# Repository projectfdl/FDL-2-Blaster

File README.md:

# FDL-2-Blaster

This is the Git repository for all things FDL-2 related. You can find all the print/STL files you need here to print your own FDL-2 as well as parts lists, wiring diagrams and firmware.

There are technically three versions of the FDL-2. The original FDL-2 with a stepper pusher motor, the FDL-2+ with the DC pusher motor, and the FDL-2X with the OLED screen and click knob.

If you are building an FDL-2+:

If you are building an FDL-2X:

If you are building an FDL-2 Original Stepper version:

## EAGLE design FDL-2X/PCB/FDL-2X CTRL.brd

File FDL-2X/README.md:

# FDL-2X-Blaster

To update FDL-2X firmware you need the following:

[Sparkfun Microview Programmer](https://www.sparkfun.com/products/12924)<br/>
[XLoader](http://xloader.russemotto.com/)<br/>
Windows computer. (There are ways to do this on a mac but I have not found a quick and easy utility to do so)<br/>
<br/>
#### Flashing your FDL-2X</br>
#### Caution!!! Flash your blaster at your own risk. Doing so is not covered by any sort of warranty. If you are not comfortable or 100% confident, consider sending your Microview to Project FDL to flash.</br>
-Remove the rear blaster cap and Microview. <br/>
-Insert the Microview programmer into the USB port on your Windows computer. <br/>
-Insert the Microview from your blaster into the programmer paying careful attention to orientation.<br/>
-The screen on your microview should point up with the USB connector facing left. There is a picture indication on the board as well.<br/>
-Run XLoader. <br/>
-Choose your desired firmware hex file. <br/>
-Select the Duemilanove/Nano(ATmega328) option under device.<br/>
-Choose the com port of your USB programmer.<br/>
-Set baud rate to 115200.<br/>
-Click upload.<br/>
-You should see the lights under the screen flickering. Flashing can take 30 seconds or longer.<br/>
-When flashing is complete you will see the FDL-2X splash screen then the speed menu as usual.<br/>
-Remove the Microview from the programmer and put it back in your FDL-2X.<br/>
-Replace the rear cap and you're good to go.<br/>

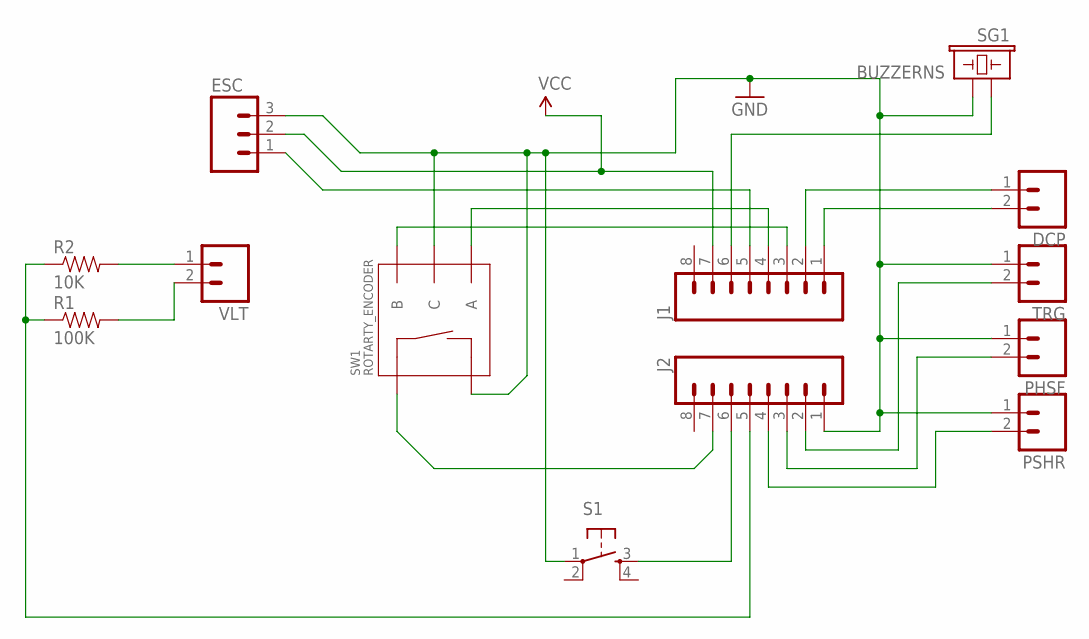
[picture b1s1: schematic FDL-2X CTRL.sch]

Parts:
DCP: M02PTH; 1X02
ESC: M03PTH; 1X03
J1, J2: M08SILK_FEMALE_PTH; 1X08
PHSF: M02PTH; 1X02
PSHR: M02PTH; 1X02
R1: 100K; AXIAL-0.3
R2: 10K; AXIAL-0.3
S1: TAC_SWITCHPTH; TACTILE-PTH
SG1: BUZZERNS; BUZZER-12MM-NS
SW1: ROTARTY_ENCODER; ROTARY_ENC_PLAIN
TRG: M02PTH; 1X02
VLT: M02PTH; 1X02

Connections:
GND: ESC.3, J2.1, PHSF.1, PSHR.1, S1.1, SG1.- (2), SW1.C, SW1.SW-, TRG.1
unnamed: ESC.1, J1.5
unnamed: J2.6, S1.3
unnamed: J2.2, TRG.2
unnamed: J2.3, PHSF.2
unnamed: J2.7, SW1.SW+
unnamed: J2.4, PSHR.2
unnamed: J1.4, SW1.A
unnamed: J1.3, SW1.B
unnamed: DCP.1, J1.2
unnamed: R2.P$2 (2), VLT.1
unnamed: DCP.2, J1.1
unnamed: R1.P$2 (2), VLT.2
unnamed: J1.6, SG1.+ (1)
unnamed: J2.5, R1.P$1 (1), R2.P$1 (1)
VCC: ESC.2, J1.7

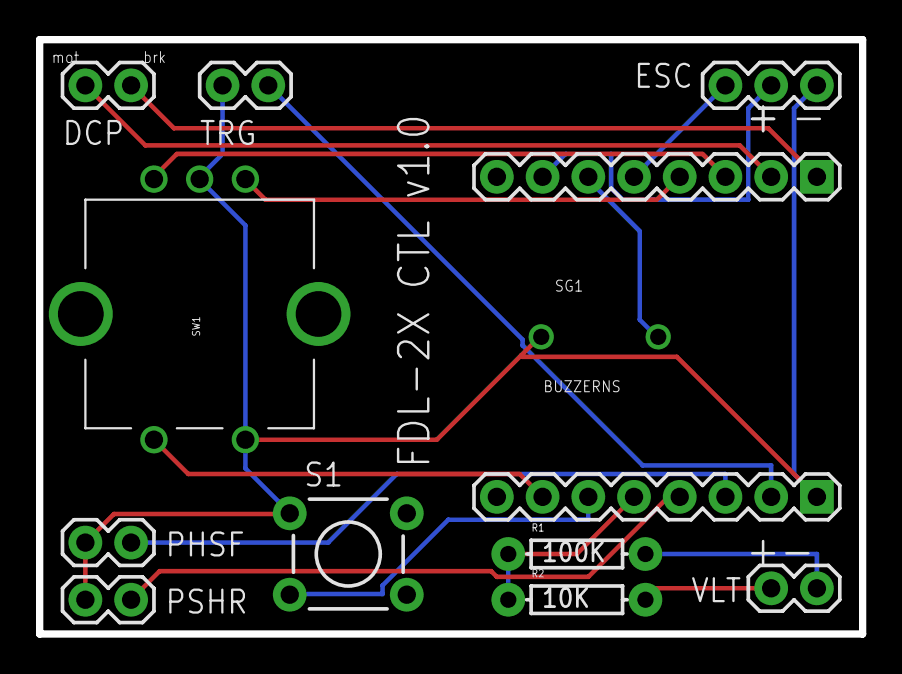
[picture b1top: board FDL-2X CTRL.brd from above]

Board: 2 copper layers, 45.7 x 33.0 mm, 13 parts (0 on the bottom side), 16 nets.

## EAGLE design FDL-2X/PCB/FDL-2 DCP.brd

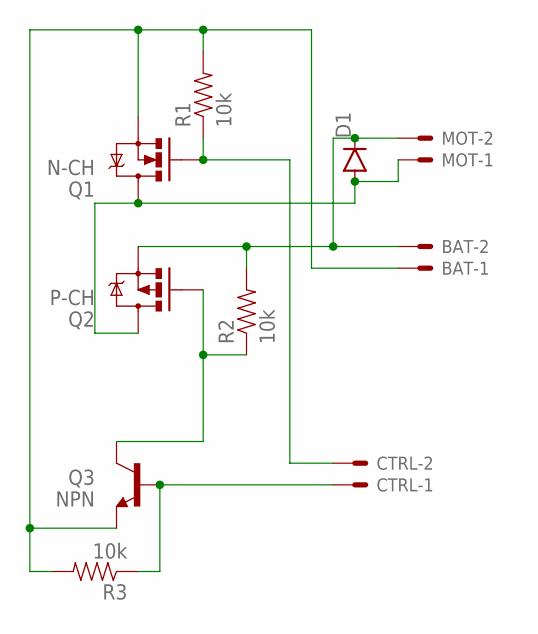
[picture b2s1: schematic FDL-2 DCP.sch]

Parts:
BAT: JST-XH-02-PIN-LONG-PAD; JST-XH-02-PACKAGE-LONG-PAD
CTRL: JST-XH-02-PIN-LONG-PAD; JST-XH-02-PACKAGE-LONG-PAD
D1: DIODEPTH; DIODE-1N4001
MOT: JST-XH-02-PIN-LONG-PAD; JST-XH-02-PACKAGE-LONG-PAD
Q1: N-CH; TO220V
Q2: P-CH; TO220V
Q3: NPN; TO-92
R1, R2, R3: 10k; AXIAL-0.3EZ

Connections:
unnamed: CTRL.1, Q3.2 (B), R3.P$1 (1)
unnamed: Q2.1 (G), Q3.3 (C), R2.P$1 (1)
unnamed: BAT.1, Q1.3 (S), Q3.1 (E), R1.P$2 (2), R3.P$2 (2)
unnamed: CTRL.2, Q1.1 (G), R1.P$1 (1)
unnamed: BAT.2, D1.C, MOT.2, Q2.3 (S), R2.P$2 (2)
unnamed: D1.A, MOT.1, Q1.2 (D), Q2.2 (D)

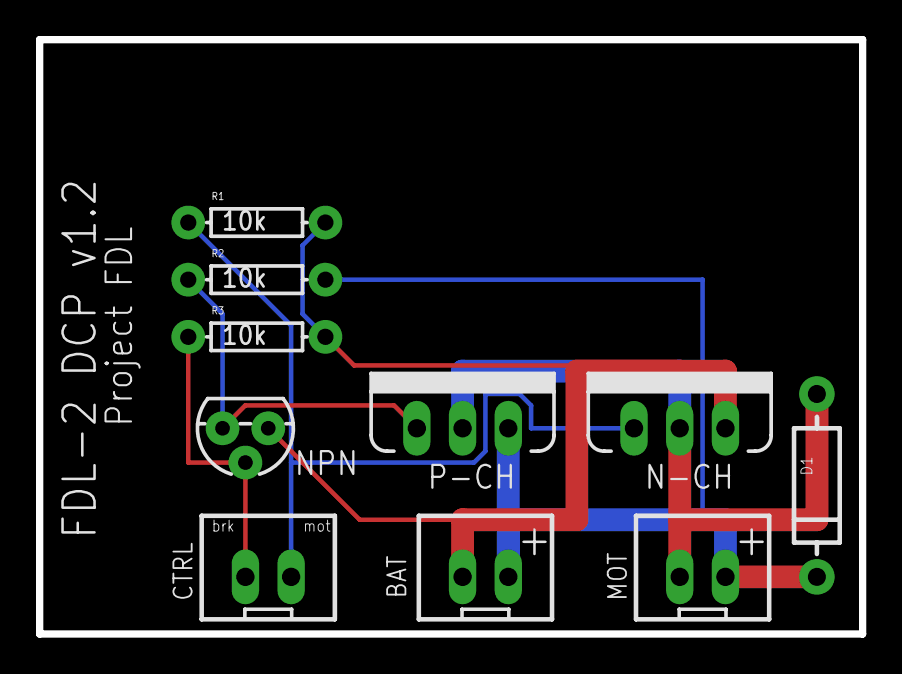
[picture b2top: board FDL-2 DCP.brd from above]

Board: 2 copper layers, 45.7 x 33.0 mm, 10 parts (0 on the bottom side), 6 nets.

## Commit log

2016-12-18 Initial commit STL, Firmware, BOM
2016-12-24 Shortening spinner bushing
2016-12-24 Extending front edges to meet outer guard.
2016-12-24 Loosening slots for better fit
2016-12-24 Adding wire guard across top to keep trigger wire away from pusher mech
2016-12-24 Updated magwell to fit Buzz Bee mags,
2017-01-16 Updating rear plate stl to accommodate longer 5pin connector housing.
2017-03-10 Adding FDL-2 wiring diagram
2017-03-10 Removing wiring diagram jpg
2017-03-10 Adding webapp firmware and html file
2017-03-10 Adding high crush flywheel stl
2017-03-14 Fixing artifacts on main barrel
2017-03-24 Updating firmware with webapp settings
2017-03-26 Updated: Main barrel - remove mesh errors Mag release - bigger button, better fit Rear plate - adjusted pusher guide lower Spinner - lengthened collar Handle guards - Better positive close and fit
2017-05-10 Adding new FDL-2 wiring diagram to match the new CTRL v1.1 PCB.
2017-05-19 Adding FDL-2+ firmware
2017-05-19 Adding FDL-2+ files
2017-12-05 File reorg for 2X
2017-12-05 Removing old files
2017-12-05 removing idea files
2017-12-05 Readme update
2018-01-15 Adding 2X firmware
2018-02-13 Adding linear stepping via torukmakto4's code. See 'http://torukmakto4.blogspot.com/2017/12/on-delay-change-per-step-pitfall-and.html'
    Also disables RoF, and always fires one at least dart per trigger pull.
2018-02-13 There is no need for a last modified field when tracked via git.
2018-02-14 Refactored everything to be neater, split across the fireBrushlessLoop function.
2018-03-24 Adding 2X wiring diagram
2018-04-01 Fixing ROF, before it would not respect what the ROF potentiometer was set to
2019-04-26 Add 2X hex file
2019-06-08 Create README.md
    Adding hex flashing readme
2021-11-18 Add 2x bom and pcb eagle files

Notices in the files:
parts and their libraries:
SparkFun-DiscreteSemi: Licensing: Creative Commons ShareAlike 4.0 International - https://creativecommons.org/licenses/by-sa/4.0
